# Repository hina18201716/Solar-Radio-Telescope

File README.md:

# Solar Radio Telescope Upgrade

The solar radio telescope is located outside the visitor center at the Very Large Array site for educational purpose for visitors. The entire system of this telescope was re-designed, detecting RF energy and displaying DC voltage on Voltmeter. Construction and installation of the electrical system were done in August 2023 by the supporting team, who confirmed that the system was sufficiently functional. However, more improvement on the dynamic range on the voltmeter and additional indications were needed to attract a wider range of visitors in regards to age and background knowledge. 

The more detailed information can be found on report. https://www.overleaf.com/read/fyrtmdrdjbmg#2ac999

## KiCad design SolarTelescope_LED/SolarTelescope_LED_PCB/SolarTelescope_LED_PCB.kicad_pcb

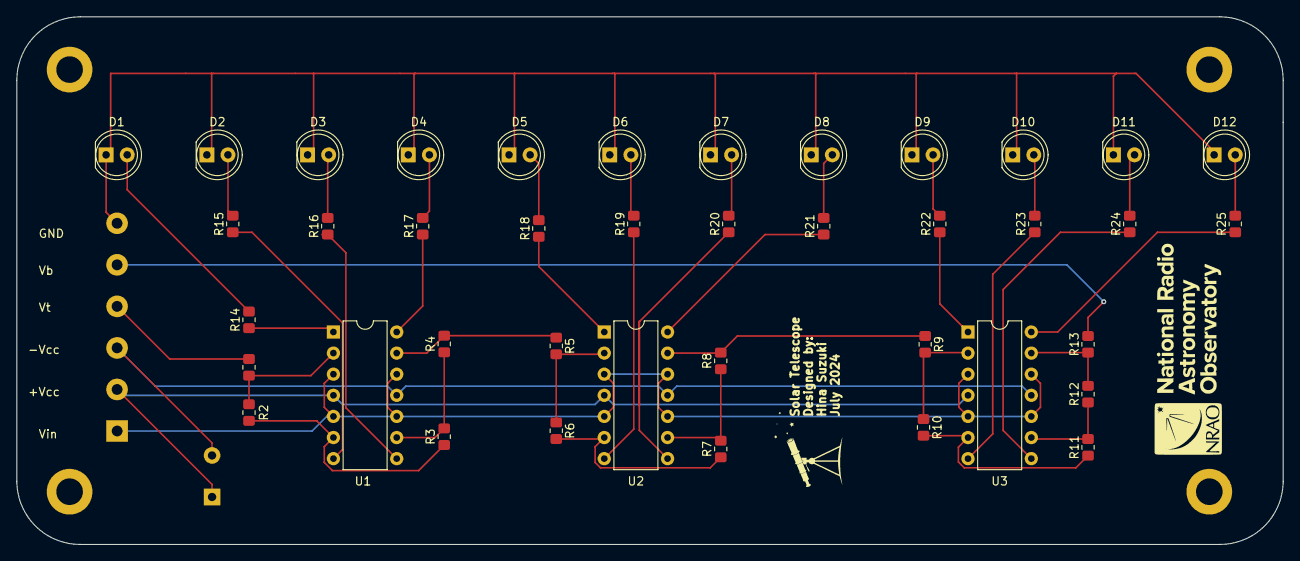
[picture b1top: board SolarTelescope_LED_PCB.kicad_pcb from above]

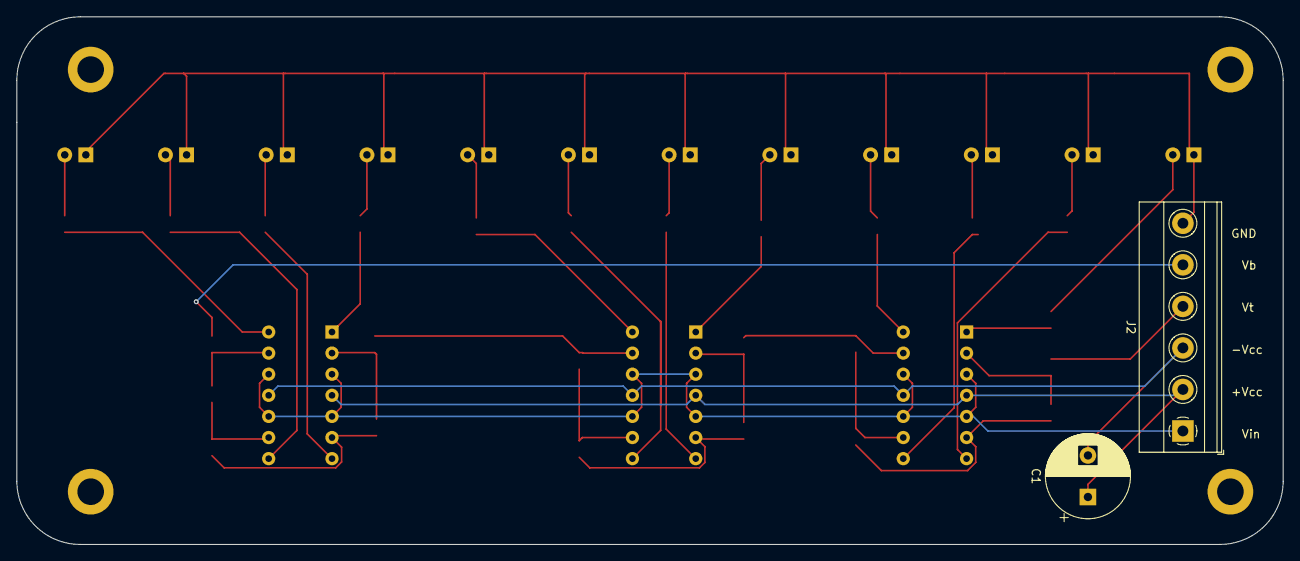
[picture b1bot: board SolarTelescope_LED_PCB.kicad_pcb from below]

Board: 2 copper layers, 152.4 x 63.5 mm, 42 parts (2 on the bottom side), 42 nets.

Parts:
C1: 1m; CP_Radial_D10.0mm_P5.00mm
D1, D2, D3, D4, D5, D6, D7, D8, D9, D10, D11, D12: LED; LED_D5.0mm
J2: Screw_Terminal_01x06; TerminalBlock_Phoenix_MKDS-1,5-6_1x06_P5.00mm_Horizontal
R1: 48k; R_0805_2012Metric_Pad1.20x1.40mm_HandSolder
R2, R3, R4, R5, R6, R7, R8, R9, R10, R11, R12, R13: 1k; R_0805_2012Metric_Pad1.20x1.40mm_HandSolder
R14, R15, R16, R17, R18, R19, R20, R21, R22, R23, R24, R25: 511; R_0805_2012Metric_Pad1.20x1.40mm_HandSolder
U1, U2, U3: LM324; DIP-14_W7.62mm

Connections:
+Vcc: C1.1, J2.2, U1.4 (V+), U2.4 (V+), U3.4 (V+)
-Vcc: C1.2, J2.3, U1.11 (V-), U2.11 (V-), U3.11 (V-)
GND: D1.1 (K), D2.1 (K), D3.1 (K), D4.1 (K), D5.1 (K), D6.1 (K), D7.1 (K), D8.1 (K), D9.1 (K), D10.1 (K), D11.1 (K), D12.1 (K), J2.6
unnamed: D1.2 (A), R14.2
unnamed: D2.2 (A), R15.2
unnamed: D3.2 (A), R16.2
unnamed: D4.2 (A), R17.2
unnamed: D5.2 (A), R18.2
unnamed: D6.2 (A), R19.2
unnamed: D7.2 (A), R20.2
unnamed: D8.2 (A), R21.2
unnamed: D9.2 (A), R22.2
unnamed: D10.2 (A), R23.2
unnamed: D11.2 (A), R24.2
unnamed: D12.2 (A), R25.2
unnamed: R14.1, U1.1
unnamed: R15.1, U1.7
unnamed: R16.1, U1.8
unnamed: R17.1, U1.14
unnamed: R18.1, U2.1
unnamed: R19.1, U2.7
unnamed: R20.1, U2.8
unnamed: R21.1, U2.14
unnamed: R22.1, U3.1
unnamed: R23.1, U3.7
unnamed: R24.1, U3.8
unnamed: R25.1, U3.14
unnamed: R1.2, R2.1, U1.2 (-)
unnamed: R2.2, R3.1, U1.6 (-)
unnamed: R3.2, R4.1, U1.9 (-)
unnamed: R4.2, R5.1, U1.13 (-)
unnamed: R5.2, R6.1, U2.2 (-)
unnamed: R6.2, R7.1, U2.6 (-)
unnamed: R7.2, R8.1, U2.9 (-)
unnamed: R8.2, R9.1, U2.13 (-)
unnamed: R9.2, R10.1, U3.2 (-)
unnamed: R10.2, R11.1, U3.6 (-)
unnamed: R11.2, R12.1, U3.9 (-)
unnamed: R12.2, R13.1, U3.13 (-)
Vbottom: J2.5, R13.2
Vin: J2.1, U1.3 (+), U1.5 (+), U1.10 (+), U1.12 (+), U2.3 (+), U2.5 (+), U2.10 (+), U2.12 (+), U3.3 (+), U3.5 (+), U3.10 (+), U3.12 (+)
Vtop: J2.4, R1.1

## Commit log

2024-07-30 added solarfinder, results, and demo
2024-08-07 latex circuitikz manual added
2024-08-08 LED array result added
2024-08-08 added new solar finder drawingq
2024-08-08 added new plots
2024-08-08 SolarFinderMount drawing added
2024-08-15 Version B.
